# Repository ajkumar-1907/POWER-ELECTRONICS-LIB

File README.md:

<div align="center">

# ⚡ power-converter-lib

**An open-source KiCad library of power electronics converters and embedded hardware.**
Every project ships with a schematic, PCB layout, Gerbers, working principle, design equations and build notes, ready to study, modify or send to fab.

[Projects](#-projects) · [Specs at a glance](#-specs-at-a-glance) · [Folder layout](#-what-each-folder-contains) · [Quick start](#-quick-start) · [Roadmap](#-roadmap)

</div>

---

## 🖼️ Gallery

Click any board to open its folder.

<table>
  <tr>
    <td align="center" width="25%">
      <br/>
      <b><a href="buck-converter/">Buck Converter</a></b><br/><sub>DC-DC · Step-down</sub>
    </td>
    <td align="center" width="25%">
      <br/>
      <b><a href="boost-converter/">Boost Converter</a></b><br/><sub>DC-DC · Step-up</sub>
    </td>
    <td align="center" width="25%">
      <br/>
      <b><a href="ac-dc-bridge-rectifier/">AC-DC Bridge Rectifier</a></b><br/><sub>AC-DC · Full-wave</sub>
    </td>
    <td align="center" width="25%">
      <br/>
      <b><a href="transformerless-power-supply/">Transformerless PSU</a></b><br/><sub>AC-DC · Capacitive dropper</sub>
    </td>
  </tr>
  <tr>
    <td align="center">
      <br/>
      <b><a href="dc-motor-speed-controller/">DC Motor Speed Controller</a></b><br/><sub>Motor control · PWM</sub>
    </td>
    <td align="center">
      <br/>
      <b><a href="servo-tester/">Servo Tester</a></b><br/><sub>Motor control · 555 PWM</sub>
    </td>
    <td align="center">
      <br/>
      <b><a href="usb-to-uart-converter/">USB to UART Converter</a></b><br/><sub>Interface · CP2102N</sub>
    </td>
    <td align="center">
      <br/>
      <b><a href="air-quality-monitor/">IoT Air Quality Monitor</a></b><br/><sub>IoT · ESP8266</sub>
    </td>
  </tr>
  <tr>
    <td align="center">
      <br/>
      <b><a href="airtap/">AirTap</a></b><br/><sub>Home automation · Touchless switch</sub>
    </td>
    <td align="center">
      <br/>
      <b><a href="dual-active-bridge/">Dual Active Bridge</a></b><br/><sub>DC-DC · Bidirectional, isolated · 3.3 kW</sub>
    </td>
  </tr>
</table>

---

## 📦 Projects

### 🔋 DC-DC Converters

| Project | Topology | Key IC | Input → Output | Highlights |
|---|---|---|---|---|
| [**Buck Converter**](buck-converter/) | Step-down (non-isolated) | LM2596S-5 | 7–40 V DC → **5 V**, 3 A | 150 kHz switcher, 33 µH inductor, Schottky freewheel |
| [**Boost Converter**](boost-converter/) | Step-up (non-isolated) | XL6009 | 5–32 V DC → **adj. up to ~35 V** | 4 A switch, 400 kHz, multi-turn trimmer, thermal-via array |
| [**Dual Active Bridge**](dual-active-bridge/) | Bidirectional, isolated (2 × full bridge) | C3M0060065K SiC + UCC21520 | **400 V ↔ 350 V**, 3.3 kW | 20 kHz phase-shift control, V2G-ready, 3 isolated domains, reinforced-isolated V/I sensing. ⚠️ High voltage |

### 🔌 AC-DC Converters

| Project | Topology | Key Parts | Input → Output | Highlights |
|---|---|---|---|---|
| [**AC-DC Bridge Rectifier**](ac-dc-bridge-rectifier/) | Full-wave bridge + C filter | 1N4007 ×4, 1000 µF | 12 V AC → **~15.6 V DC** (unregulated) | Bleeder resistor, LED indicator, THT-only |
| [**Transformerless Power Supply**](transformerless-power-supply/) | Capacitive dropper + LDO | X2 2.2 µF, LM7805 | 230 V AC → **5 V DC** | ⚠️ Non-isolated, mains voltage. Read the design notes |

### ⚙️ Motor Control & Signal

| Project | Topology | Key IC | Supply | Highlights |
|---|---|---|---|---|
| [**DC Motor Speed Controller**](dc-motor-speed-controller/) | 555 PWM + low-side switch | NE555 + TIP122 | 5–15 V DC, up to ~3 A | Constant-frequency PWM, 1–99 % duty, flyback diode |
| [**Servo Tester**](servo-tester/) | 555 astable, diode-steered | NE555 | 6 V DC | ~0.85–2.4 ms pulse, pot control, no code needed |

### 🧩 Interface & IoT

| Project | Function | Key IC | Supply | Highlights |
|---|---|---|---|---|
| [**USB to UART Converter**](usb-to-uart-converter/) | USB-C ↔ serial bridge | CP2102N | USB 5 V | ESD protection, TX/RX LEDs, DTR auto-reset |
| [**IoT Air Quality Monitor**](air-quality-monitor/) | Wi-Fi gas-sensing node | ESP-12E + MQ-135 | USB-C / Li-ion | TP4056 charger, MT3608 boost, CH340C auto-flash, OLED |

### 🏠 Home Automation

| Project | Function | Key IC | Supply | Highlights |
|---|---|---|---|---|
| [**AirTap**](airtap/) | Touchless AC relay switch | ATmega328 + VL53L0X | 220 V AC (HLK-5M05) | Hand-wave switching (10–30 mm), fused + MOV-protected, relay/buzzer/LEDs, test firmware. Fork of [ProxiWave-D](https://github.com/ampnics/Proxiwave-D) (MIT) |

---

## 📊 Specs at a glance

| Project | Category | Board Size | Layers | Assembly | 3D Views | KiCad Source |
|---|---|---|:---:|---|:---:|:---:|
| [Buck Converter](buck-converter/) | DC-DC | 51 × 36 mm | 2 | SMD + THT | — | ✅ |
| [Boost Converter](boost-converter/) | DC-DC | 45 × 20 mm | 2 | SMD + THT | ✅ | ✅ |
| [AC-DC Bridge Rectifier](ac-dc-bridge-rectifier/) | AC-DC | 34.6 × 30.1 mm | 2 | THT | — | ⏳ Gerbers only |
| [Transformerless PSU](transformerless-power-supply/) | AC-DC | 48.8 × 37.5 mm | 2 | THT | — | ✅ |
| [DC Motor Speed Controller](dc-motor-speed-controller/) | Motor control | 56.5 × 29 mm | 2 | THT | ✅ | ✅ |
| [Servo Tester](servo-tester/) | Signal | 30.5 × 27.8 mm | 2 | THT | — | ✅ |
| [USB to UART Converter](usb-to-uart-converter/) | Interface | 31 × 15 mm | 2 | SMD (0201, QFN) | — | ✅ |
| [IoT Air Quality Monitor](air-quality-monitor/) | IoT | 68 × 47.4 mm | 2 | SMD + THT | ✅ | ✅ |
| [AirTap](airtap/) | Home automation | 50 × 100 mm | 2 | SMD + THT | ✅ | ✅ |
| [Dual Active Bridge](dual-active-bridge/) | DC-DC (isolated) | 220 × 150 mm | 4 | SMD + THT | ✅ | ✅ |

---

## 🗂️ What each folder contains

Every project follows the same layout, so once you know one you know them all:

```
<project-name>/
├── README.md                     ← overview, working principle, equations, BOM, design notes
├── <project-name>.kicad_pro      ← KiCad project
├── <project-name>.kicad_sch      ← schematic source
├── <project-name>.kicad_pcb      ← PCB layout source
├── <project-name>-PTH.drl        ← plated drill file
├── <project-name>-NPTH.drl       ← non-plated drill file
├── gerbers/                      ← fab-ready Gerber set
├── schematic.png / .svg          ← schematic preview
├── pcb-layout2.png               ← KiCad editor-style layout
├── pcb-layout.png                ← top & bottom render
└── pcb-3d-*.png                  ← 3D renders (where available)
```

Each project README follows the same outline: **Overview → Working Principle → Key Equations → Applications → Specifications → BOM → Design Notes → Pros & Cons → Files → How to Use**.

---

## 🚀 Quick start

```bash
# 1. Clone the library
git clone https://github.com/ajkumar-1907/power-converter-lib.git
cd power-converter-lib

# 2. Open any project in KiCad 10+
#    e.g. boost-converter/boost-converter.kicad_pro
```

### 🏭 Ordering a PCB

1. Open the project folder you want.
2. Zip the contents of `gerbers/` **together with** the two `.drl` files.
3. Upload the zip to any PCB fab (JLCPCB, PCBWay, etc.). The default 2-layer, 1.6 mm FR-4 settings work for every board here except the Dual Active Bridge, which needs **4 layers, 2 oz copper**.
4. **Read the project's Design Notes before ordering.** Some boards list parts that need values set or ratings checked.

---

## 🤝 Contributing

Contributions are welcome: new topologies, layout improvements, corrections to equations or BOMs.

1. Fork the repo and create a branch (`git checkout -b add-sepic-converter`).
2. Add your project as a new folder that follows the [standard layout](#-what-each-folder-contains).
3. Open a pull request describing the design and how it was verified.

Found a mistake? [Open an issue](https://github.com/ajkumar-1907/power-converter-lib/issues).

---

## ⚠️ Safety

Several projects work with **mains voltage** or **high currents**. The Transformerless Power Supply and AirTap connect directly to mains, the Dual Active Bridge runs at **400 V DC** with large stored capacitor energy, and the Transformerless Power Supply in particular is **not isolated**: every point on it, including the output, can be at lethal potential. Only build these if you understand the risks, and always read each project's Design Notes first.

---

## 📄 License

Released under the [MIT License](LICENSE): free to use, modify and build on, including commercially.

<div align="center">

Designed by **[Anuj Kumar](https://github.com/ajkumar-1907)**, B.Tech Electrical Engineering, Delhi Technological University

⭐ If this library helped you, consider starring the repo!

</div>

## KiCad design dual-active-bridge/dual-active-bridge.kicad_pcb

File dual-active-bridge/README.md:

# Dual Active Bridge (DAB): 3.3 kW Bidirectional DC-DC Converter

A **3.3 kW, 400 V ↔ 350 V bidirectional isolated DC-DC power stage** for EV battery charging with **V2G (vehicle-to-grid)** capability. The board has two SiC full bridges connected through an off-board high-frequency transformer and series inductor. Power flows in either direction, set by the phase shift between the two bridges.

> **B.Tech Major Project-I (2026-27)**, Dept. of Electrical Engineering, Delhi Technological University. Anuj Kumar (23EE039) and Ankush (23EE033).

> ⚠️ **DANGER: 400 V DC.** The DC-link and battery capacitors store lethal energy and stay charged after power is removed. Bring the board up step by step (see [How to Use](#how-to-use)) and always measure before touching.

### 3D views

| Top | Bottom |
|---|---|
|  |  |

### Schematic sections

| Bridge 1 (primary, 400 V) | Bridge 2 (secondary, 350 V) |
|---|---|
|  |  |
| **Isolated gate drive** | **Isolated V / I sensing** |
|  |  |

### Layer views (4-layer)

| L1 Front copper | L4 Back copper |
|---|---|
|  |  |
| **L2 In1: V1+ / V2+ / GND planes** | **L3 In2: PGND1 / PGND2 / +5 V planes** |
|  |  |

## Overview

| Block | Parts | Function |
|---|---|---|
| **Bridge 1 (primary)** | Q1–Q4 C3M0060065K, C1 100 µF/450 V, C3/C4 film + C7/C8 1812 | 400 V DC bus full bridge: legs A and B |
| **Bridge 2 (secondary)** | Q5–Q8 C3M0060065K, C2 150 µF/450 V, C5/C6 film + C9/C10 1812 | 350 V battery-side full bridge: legs C and D |
| **Gate drive** | U1–U4 UCC21520DW, PS1–PS8 MGJ2D051505SC | One dual isolated driver per leg and one isolated +15 / −5 V supply per switch (Kelvin-source return) |
| **Voltage sensing** | R30–R41 dividers, U5/U6 AMC1311B, PS9/PS10 + U7/U8 | Reinforced-isolated V1 and V2 measurement for the controller ADC |
| **Current sensing** | CS1/CS2 LEM LTSR 25-NP | Battery current (I_BAT) and transformer current (I_XFMR) |
| **Protection** | F1/F2 20 A 500 VDC fuses, R46/R47 220 k bleeders | Input/output fusing and capacitor discharge |
| **Control interface** | J9 2×10 header, J10 aux 5 V, D9/D10 OR-ing, U9 3.3 V LDO | 8 PWM inputs, enable, sense outputs to a C2000 LaunchPad |
| **Power terminals** | J1–J8 M4 bolt pads | DC bus ±, battery ±, transformer a/b (primary) and c/d (secondary) |

The board is split into **three isolated domains**:
- **Primary** (PGND1, 400 V)
- **Secondary** (PGND2, 350 V)
- **Control** (GND, 3.3/5 V)

Only the isolators cross between domains. Each one sits over a **2 mm routed slot**, with **≥ 8 mm** creepage/clearance between domains.

## Working Principle

1. **Two square waves.** Each full bridge switches at **20 kHz** with 50 % duty, diagonal pairs together (Q1+Q4 / Q2+Q3 on the primary, Q5+Q8 / Q6+Q7 on the secondary). Bridge 1 puts ±V1 on the transformer primary, and Bridge 2 puts ±V2 on the secondary.
2. **Phase shift sets power.** The controller delays Bridge 2 relative to Bridge 1 by a phase angle φ. The voltage difference across the series inductance Lk drives the current that transfers power.
3. **Bidirectional flow.** If φ > 0 (Bridge 1 leads), power flows from the DC bus to the battery (charging, G2V). If φ < 0, power flows from the battery back to the bus (V2G). The hardware is identical in both directions.
4. **Soft switching.** With the turns ratio matched to the voltages (d = n·V2 / V1 ≈ 1), the inductor current commutates each switch's output capacitance during the dead time. This gives **zero-voltage switching (ZVS)** over most of the load range.
5. **Isolation.** The 8:7 transformer gives galvanic isolation between bus and battery. The control side is isolated from both through the drivers, the AMC1311s and the LEM sensors.

## J9: Control Header (2×10, to the controller)

| Pin | Signal | Pin | Signal |
|---|---|---|---|
| 1 | PWM1 (Q1) | 2 | PWM2 (Q2) |
| 3 | PWM3 (Q3) | 4 | PWM4 (Q4) |
| 5 | PWM5 (Q5) | 6 | PWM6 (Q6) |
| 7 | PWM7 (Q7) | 8 | PWM8 (Q8) |
| 9 | GND | 10 | GND |
| 11 | DIS (low = enable) | 12 | reserved (fault) |
| 13 | V1 sense + | 14 | V1 sense − |
| 15 | V2 sense + | 16 | V2 sense − |
| 17 | I_BAT | 18 | I_XFMR |
| 19 | +5 V | 20 | GND |

PWMn drives Qn directly. The controller firmware creates the diagonal pairing and the phase shift. Each UCC21520 also adds a hardware dead-time floor of about **500 ns** (R_DT = 49.9 k). DIS is pulled up, so all drivers stay **off** until the controller pulls DIS low.

## Key Equations

**Power transfer (single phase shift):**
```
P = n·V1·V2·φ·(π − |φ|) / (2π²·fs·Lk)        φ in rad, n = N1/N2 = 8/7

P_max (φ = π/2) = n·V1·V2 / (8·fs·Lk)
               = (8/7)(400)(350) / (8 · 20 kHz · 291 µH) ≈ 3.44 kW
At 3.3 kW:  φ ≈ 72°  (≈ 10 µs of the 50 µs period)
```

**Voltage conversion ratio (ZVS condition):**
```
d = n·V2 / V1 = (8/7)(350) / 400 = 1.0     → ZVS on both bridges over a wide load range
```

**Dead time (UCC21520):**
```
t_DT ≈ 10 ns/kΩ × R_DT = 10 × 49.9 k ≈ 500 ns     (1 % of the 50 µs period)
```

**Voltage sense divider (per bus):**
```
V_sense = V_bus × 8.06 k / (5 × 402 k + 8.06 k)  → 500 V gives 2.0 V (AMC1311 full scale)
```

## Applications

- On-board / off-board EV chargers with **V2G / V2H** capability
- Battery energy storage interfaces (bidirectional DC bus ↔ battery)
- Isolated DC-DC stage after a PFC front end
- Teaching and research platform for DAB modulation (SPS, EPS, DPS, TPS)

## Specifications

| Parameter | Value |
|---|---|
| DC bus (V1) | 400 V DC |
| Battery (V2) | 350 V nominal (300 V min) |
| Rated power | 3.3 kW, bidirectional |
| Switching frequency | 20 kHz |
| Transformer | 8:7, off-board (ETD59 / E65 core) |
| Series inductance Lk | 291 µH, off-board (or transformer leakage) |
| Switches | 8 × Wolfspeed C3M0060065K SiC, 650 V / 60 mΩ, TO-247-4 Kelvin source |
| Gate drive | +15 V / −5 V, 10 Ω on / 4.7 Ω off, 500 ns dead time |
| Isolation | 3 domains, ≥ 8 mm creepage, 2 mm slots under every isolator |
| Control | 3.3 V logic, C2000 LaunchPad (or any MCU with 8 PWM outputs) |
| Board | 220 × 150 mm, **4-layer**, 1.6 mm FR-4, **2 oz copper on all layers**, 6 mounting/heatsink holes |

## Bill of Materials (key parts)

| Ref | Value | Package |
|---|---|---|
| Q1–Q8 | Wolfspeed C3M0060065K (650 V, 60 mΩ SiC) | TO-247-4 |
| U1–U4 | TI UCC21520DW dual isolated gate driver | SOIC-16W |
| PS1–PS10 | Murata MGJ2D051505SC (5 V → +15 / −5 V, 5.2 kV) | SIP (THT) |
| U5, U6 | TI AMC1311BDWV reinforced isolated amplifier | SOIC-8 wide |
| CS1, CS2 | LEM LTSR 25-NP closed-loop current sensor | THT |
| C1 | 100 µF 450 V (Nichicon LGN2W101MELZ25) | Snap-in Ø25 |
| C2 | 150 µF 450 V (Nichicon LGN2W151MELZ30) | Snap-in Ø25 |
| C3–C6 | 1 µF 630 V polypropylene film (WIMA MKS4) | P22.5 mm |
| C7–C10 | 100 nF 1 kV X7R (KEMET C1812C104KDRAC) | 1812 |
| D1–D8 | BAT54J turn-off diode | SOD-323F |
| F1, F2 | 20 A 500 VDC fuse (Littelfuse 505) + clips | 6.3 × 32 mm |
| R46, R47 | 220 k 2 W bleeder | Axial |
| U7, U8 / U9 | 78L05 / AP2112K-3.3 | SOT-89 / SOT-23-5 |
| J9 / J10 | 2×10 2.54 mm header / Phoenix MKDS 2-way 5.08 mm | THT |
| J1–J8 | M4 ring-lug bolt pads | Ø4.3 mm plated |

The full BOM is 174 parts. 0805/1206 passives and their values are shown in the schematic.

## Design Notes

- **Off-board magnetics:** the transformer (8:7) and Lk (291 µH) connect through the M4 bolt pads: a/b to the primary, c/d to the secondary. Size the wires for the RMS current at 3.3 kW.
- **Kelvin source:** every MOSFET has its own isolated supply, referenced to its own Kelvin pin, so 8 supplies in total. Sharing a supply between low-side switches would tie the Kelvin pins together and defeat the Kelvin connection.
- **Commutation loop:** each leg has a film capacitor (top) and a 1 kV 1812 (bottom) placed directly at the MOSFET drain/source pins. V+ and PGND are laminated on In1/In2 to keep loop inductance low.
- **Isolation rules:** the custom DRC file (`dual-active-bridge.kicad_dru`) enforces:
  - 3 mm between different potentials inside a power domain;
  - 8 mm between domains;
  - 2 mm from HV copper to edges and slots.
  
  Netclasses are named `<domain>_<kind>_<potential>`.
- **Gate supply voltage:** the MGJ2D051505SC gives +15 / −5 V. For the recommended −4 V turn-off of the C3M series, use a −4 V variant or add a zener.
- **J9 pin 12** is reserved. The UCC21520 has no fault output, so the pin is free for a future over-current comparator.
- **Aux 5 V (J10):** the 10 isolated supplies draw about 0.5 A, which is more than a LaunchPad's 5 V pin can supply. J10 and J9 +5 V are OR-ed through D9/D10.
- **Heatsinks:** Q1–Q4 and Q5–Q8 mount on two separate heatsinks (H5/H6 mounting holes), one per isolated domain. Use insulating pads.
- **Before ordering:** check the footprints against their datasheets, especially:
  - the TO-247-4 pin order (1 D, 2 S, 3 Kelvin S, 4 G);
  - the AMC1311 DWV pin-out;
  - the fuse clips.

## Pros & Cons

| Pros | Cons |
|---|---|
| Bidirectional with identical hardware (G2V and V2G) | 8 active switches, 8 isolated gate supplies |
| Galvanic isolation and ZVS at d ≈ 1, giving high efficiency | ZVS is lost at light load or when d ≠ 1 (needs EPS/DPS/TPS modulation) |
| Simple single-phase-shift control | High circulating (reactive) current at light load |
| SiC + Kelvin source: fast, clean switching | Off-board magnetics must be designed and wound separately |
| Reinforced-isolated sensing, ready for closed-loop control | 4-layer, 2 oz board: higher fab cost |

## Files in This Folder

| File | Description |
|---|---|
| `dual-active-bridge.kicad_pro` / `.kicad_sch` / `.kicad_pcb` | KiCad 10 project, root schematic and PCB |
| `Bridge1` / `Bridge2` / `GateDrive` / `Sensing` / `Connectors.kicad_sch` | Hierarchical sub-sheets |
| `dual-active-bridge.kicad_dru` | Custom HV / isolation design rules |
| `DAB_3k3W.kicad_sym` / `DAB_3k3W.pretty/` | Project symbol library and fuse-clip footprint (loaded through `sym-lib-table` / `fp-lib-table`) |
| `dual-active-bridge-PTH.drl` / `dual-active-bridge-NPTH.drl` | Drill files |
| `gerbers/` | Gerber set for fabrication: 4 copper layers, masks, paste, silkscreen, Edge.Cuts with isolation slots, job file |
| `schematic.pdf` | Full 6-sheet schematic |
| `schematic.png` / `schematic-*.png` | Root sheet and section images |
| `pcb-3d-top.png` / `pcb-3d-bottom.png` / `pcb-3d-angle.png` / `pcb-3d-angle-rear.png` | 3D renders |
| `pcb-layout2.png` / `pcb-layout.png` | Layout previews |
| `pcb-front-copper.png` / `pcb-back-copper.png` / `pcb-inner1-copper.png` / `pcb-inner2-copper.png` | Copper layer views |

## How to Use

1. Open `dual-active-bridge.kicad_pro` in [KiCad](https://www.kicad.org/) 10 or later.
2. **To manufacture:**
   - Zip `gerbers/` together with the two `.drl` files and upload the zip.
   - Order **4 layers, 1.6 mm, 2 oz copper on all layers**.
   - In the order notes, mention that the board has **internal routed slots**. They are drawn on Edge.Cuts.
3. **Assemble:** the 1812 capacitors C7–C10 are on the bottom side. Mount Q1–Q8 on insulated heatsinks.
4. **Bring up in stages:**
   1. 5 V only: check every gate waveform with DIS low and no HV applied.
   2. 24–48 V on V1, current-limited, with a resistive load on V2.
   3. Step up to 400 V under supervision, behind a shield, with the fuses fitted.
5. **Close the loop:** read V1, V2, I_BAT and I_XFMR on the controller's ADC and regulate power with the phase shift φ.

## License

Released under the repository's [MIT License](../LICENSE).

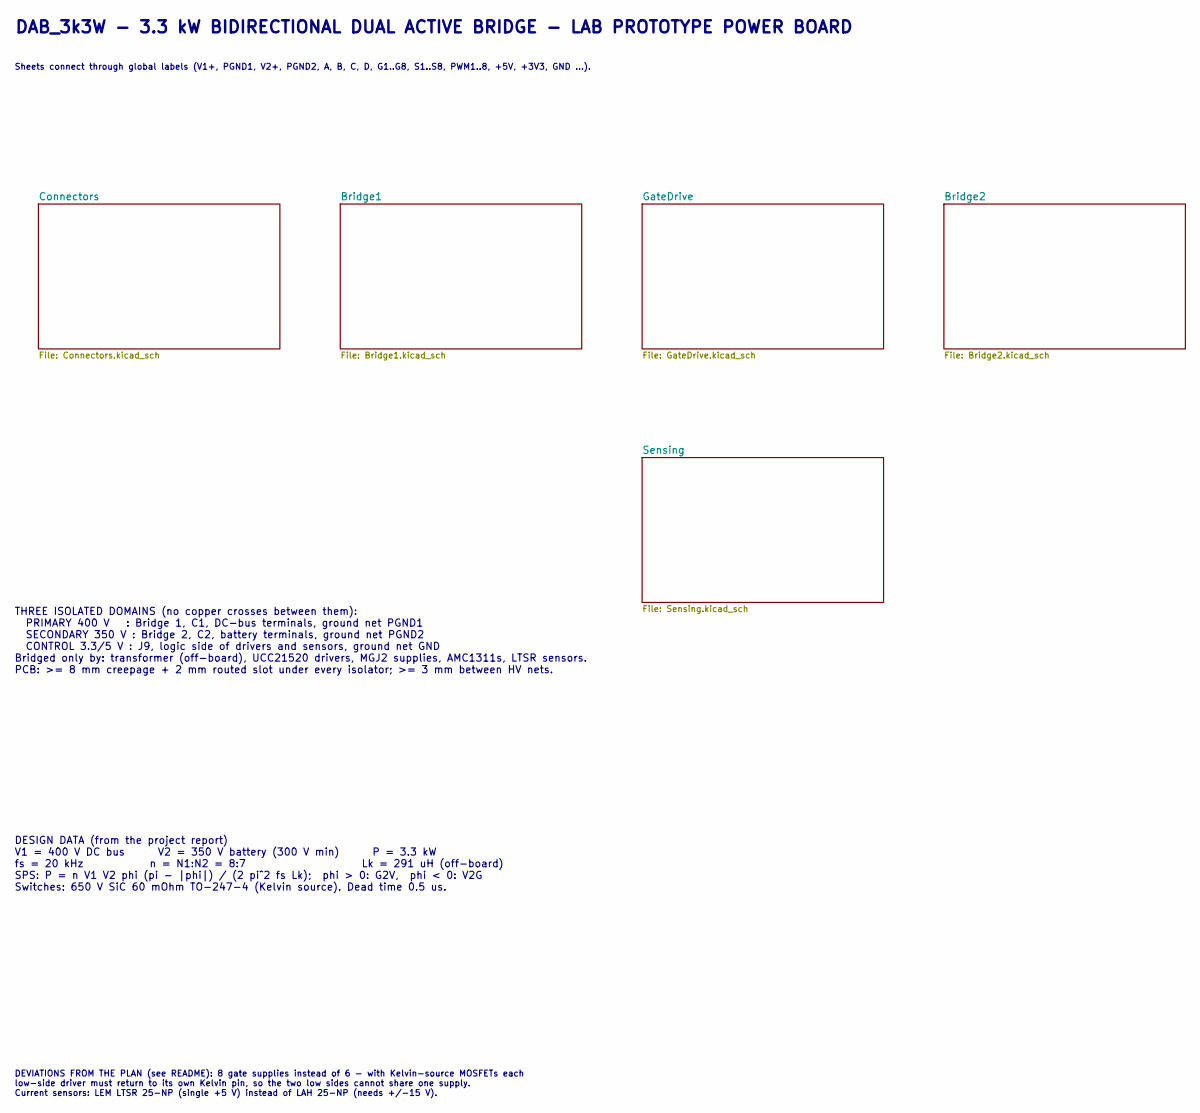
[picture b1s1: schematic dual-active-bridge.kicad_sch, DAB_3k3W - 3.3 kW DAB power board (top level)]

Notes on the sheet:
DEVIATIONS FROM THE PLAN (see README): 8 gate supplies instead of 6 - with Kelvin-source MOSFETs each low-side driver must return to its own Kelvin pin, so the two low sides cannot share one supply. Current sensors: LEM LTSR 25-NP (single +5 V) instead of LAH 25-NP (needs +/-15 V).
DAB_3k3W - 3.3 kW BIDIRECTIONAL DUAL ACTIVE BRIDGE - LAB PROTOTYPE POWER BOARD
Sheets connect through global labels (V1+, PGND1, V2+, PGND2, A, B, C, D, G1..G8, S1..S8, PWM1..8, +5V, +3V3, GND ...).
DESIGN DATA (from the project report) V1 = 400 V DC bus V2 = 350 V battery (300 V min) P = 3.3 kW fs = 20 kHz n = N1:N2 = 8:7 Lk = 291 uH (off-board) SPS: P = n V1 V2 phi (pi - |phi|) / (2 pi^2 fs Lk); phi > 0: G2V, phi < 0: V2G Switches: 650 V SiC 60 mOhm TO-247-4 (Kelvin source). Dead time 0.5 us.
THREE ISOLATED DOMAINS (no copper crosses between them): PRIMARY 400 V : Bridge 1, C1, DC-bus terminals, ground net PGND1 SECONDARY 350 V : Bridge 2, C2, battery terminals, ground net PGND2 CONTROL 3.3/5 V : J9, logic side of drivers and sensors, ground net GND Bridged only by: transformer (off-boa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

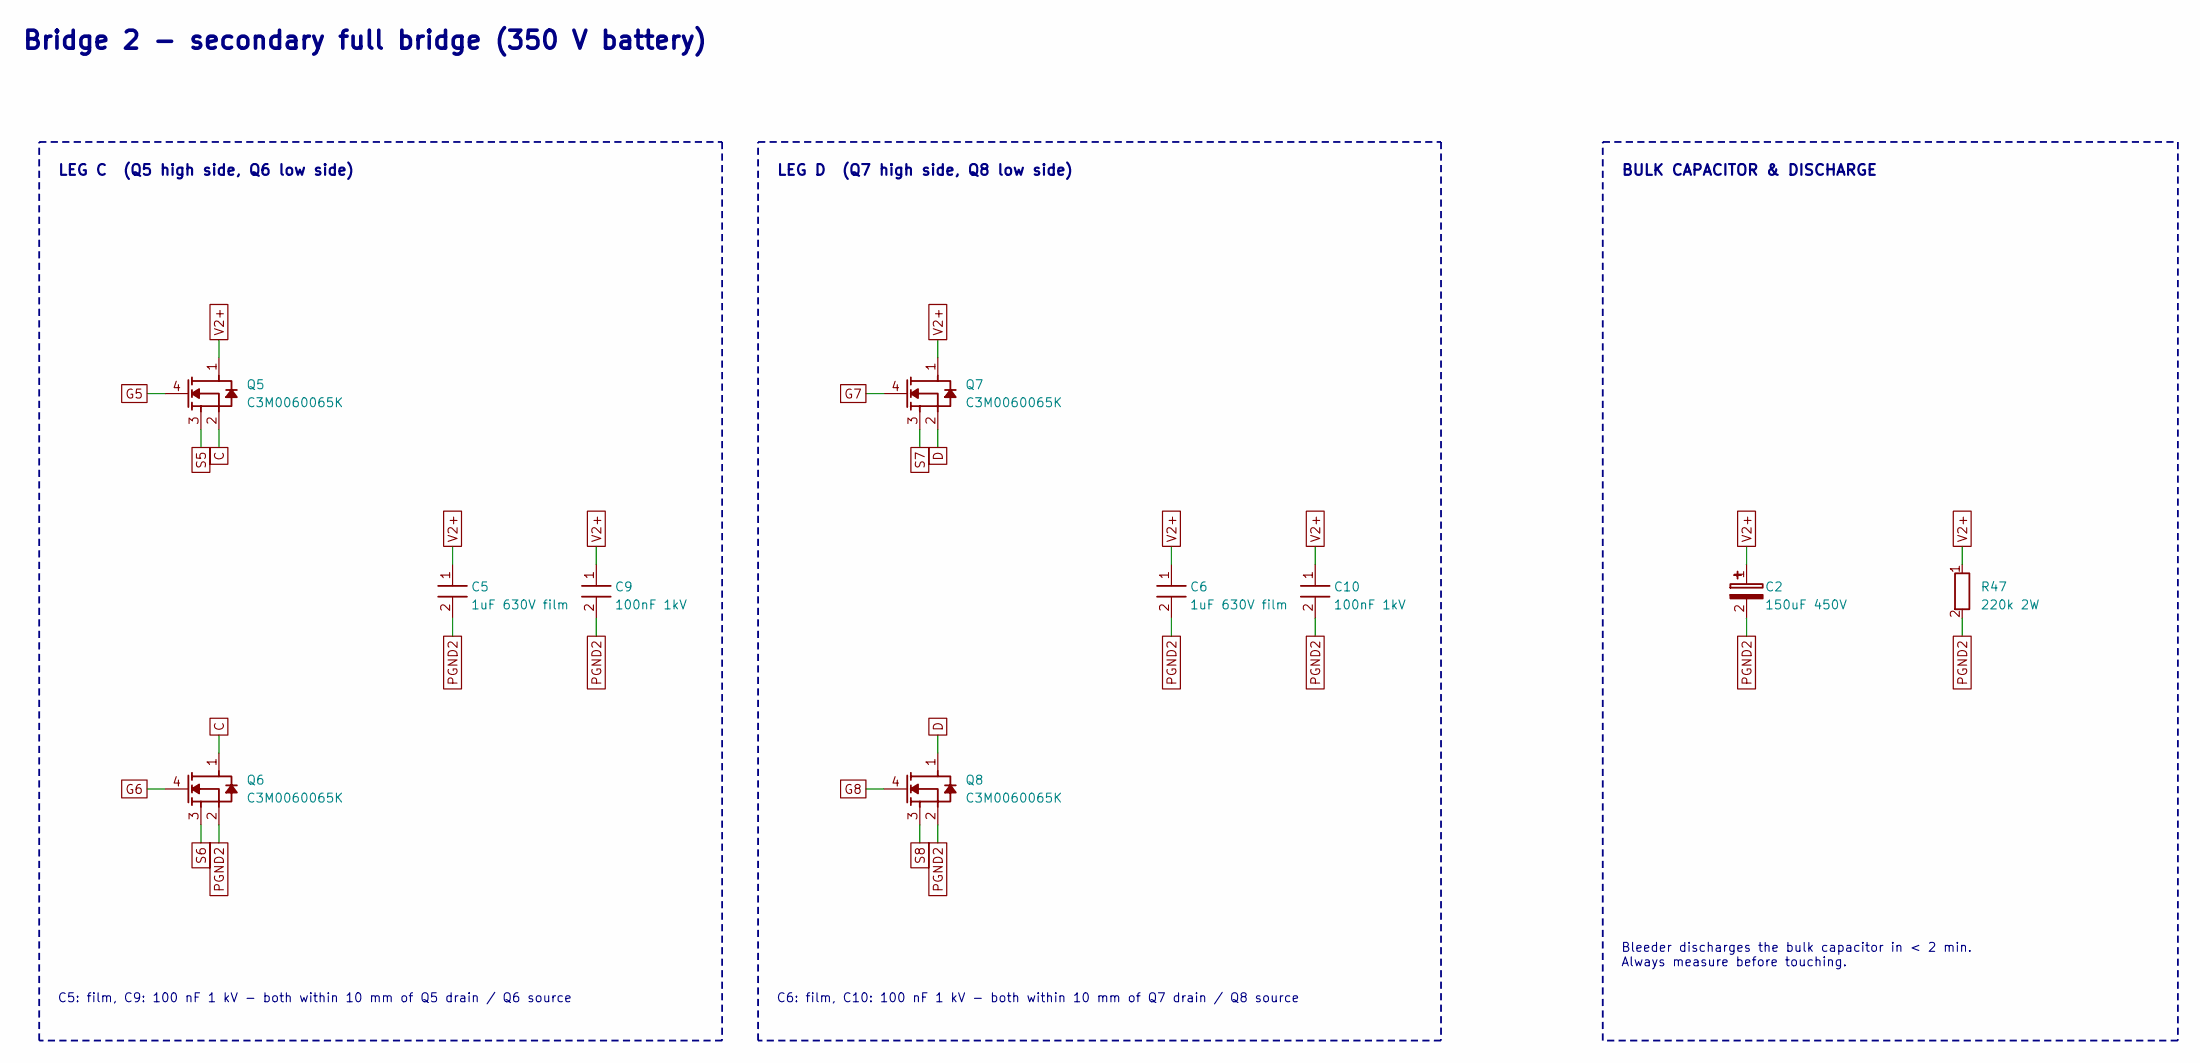
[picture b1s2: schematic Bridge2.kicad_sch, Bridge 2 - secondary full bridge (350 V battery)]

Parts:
C2: 150uF 450V; CP_Radial_D25.0mm_P10.00mm_SnapIn; MPN Nichicon LGN2W151MELZ30
C5, C6: 1uF 630V film; C_Rect_L26.5mm_W11.5mm_P22.50mm_MKS4; MPN WIMA MKS4 1uF 630VDC, P22.5 (or KEMET R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
C9, C10: 100nF 1kV; C_1812_4532Metric; MPN KEMET C1812C104KDRAC (1 kV X7R)
Q5, Q6, Q7, Q8: C3M0060065K; TO-247-4_Vertical; MPN Wolfspeed C3M0060065K
R47: 220k 2W; R_Axial_DIN0617_L17.0mm_D6.0mm_P25.40mm_Horizontal; MPN Vishay PR02000202203JR500

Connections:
C: Q5.2 (S), Q6.1 (D); also elsewhere on the board
D: Q7.2 (S), Q8.1 (D); also elsewhere on the board
G5: Q5.4 (G); also elsewhere on the board
G6: Q6.4 (G); also elsewhere on the board
G7: Q7.4 (G); also elsewhere on the board
G8: Q8.4 (G); also elsewhere on the board
PGND2: C2.2, C5.2, C6.2, C9.2, C10.2, Q6.2 (S), Q8.2 (S), R47.2; also elsewhere on the board
S5: Q5.3 (KS); also elsewhere on the board
S6: Q6.3 (KS); also elsewhere on the board
S7: Q7.3 (KS); also elsewhere on the board
S8: Q8.3 (KS); also elsewhere on the board
V2+: C2.1, C5.1, C6.1, C9.1, C10.1, Q5.1 (D), Q7.1 (D), R47.1; also elsewhere on the board

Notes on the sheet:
Bridge 2 - secondary full bridge (350 V battery)
LEG C (Q5 high side, Q6 low side)
C6: film, C10: 100 nF 1 kV - both within 10 mm of Q7 drain / Q8 source
LEG D (Q7 high side, Q8 low side)
Bleeder discharges the bulk capacitor in < 2 min. Always measure before touching.
C5: film, C9: 100 nF 1 kV - both within 10 mm of Q5 drain / Q6 source
BULK CAPACITOR & DISCHARGE

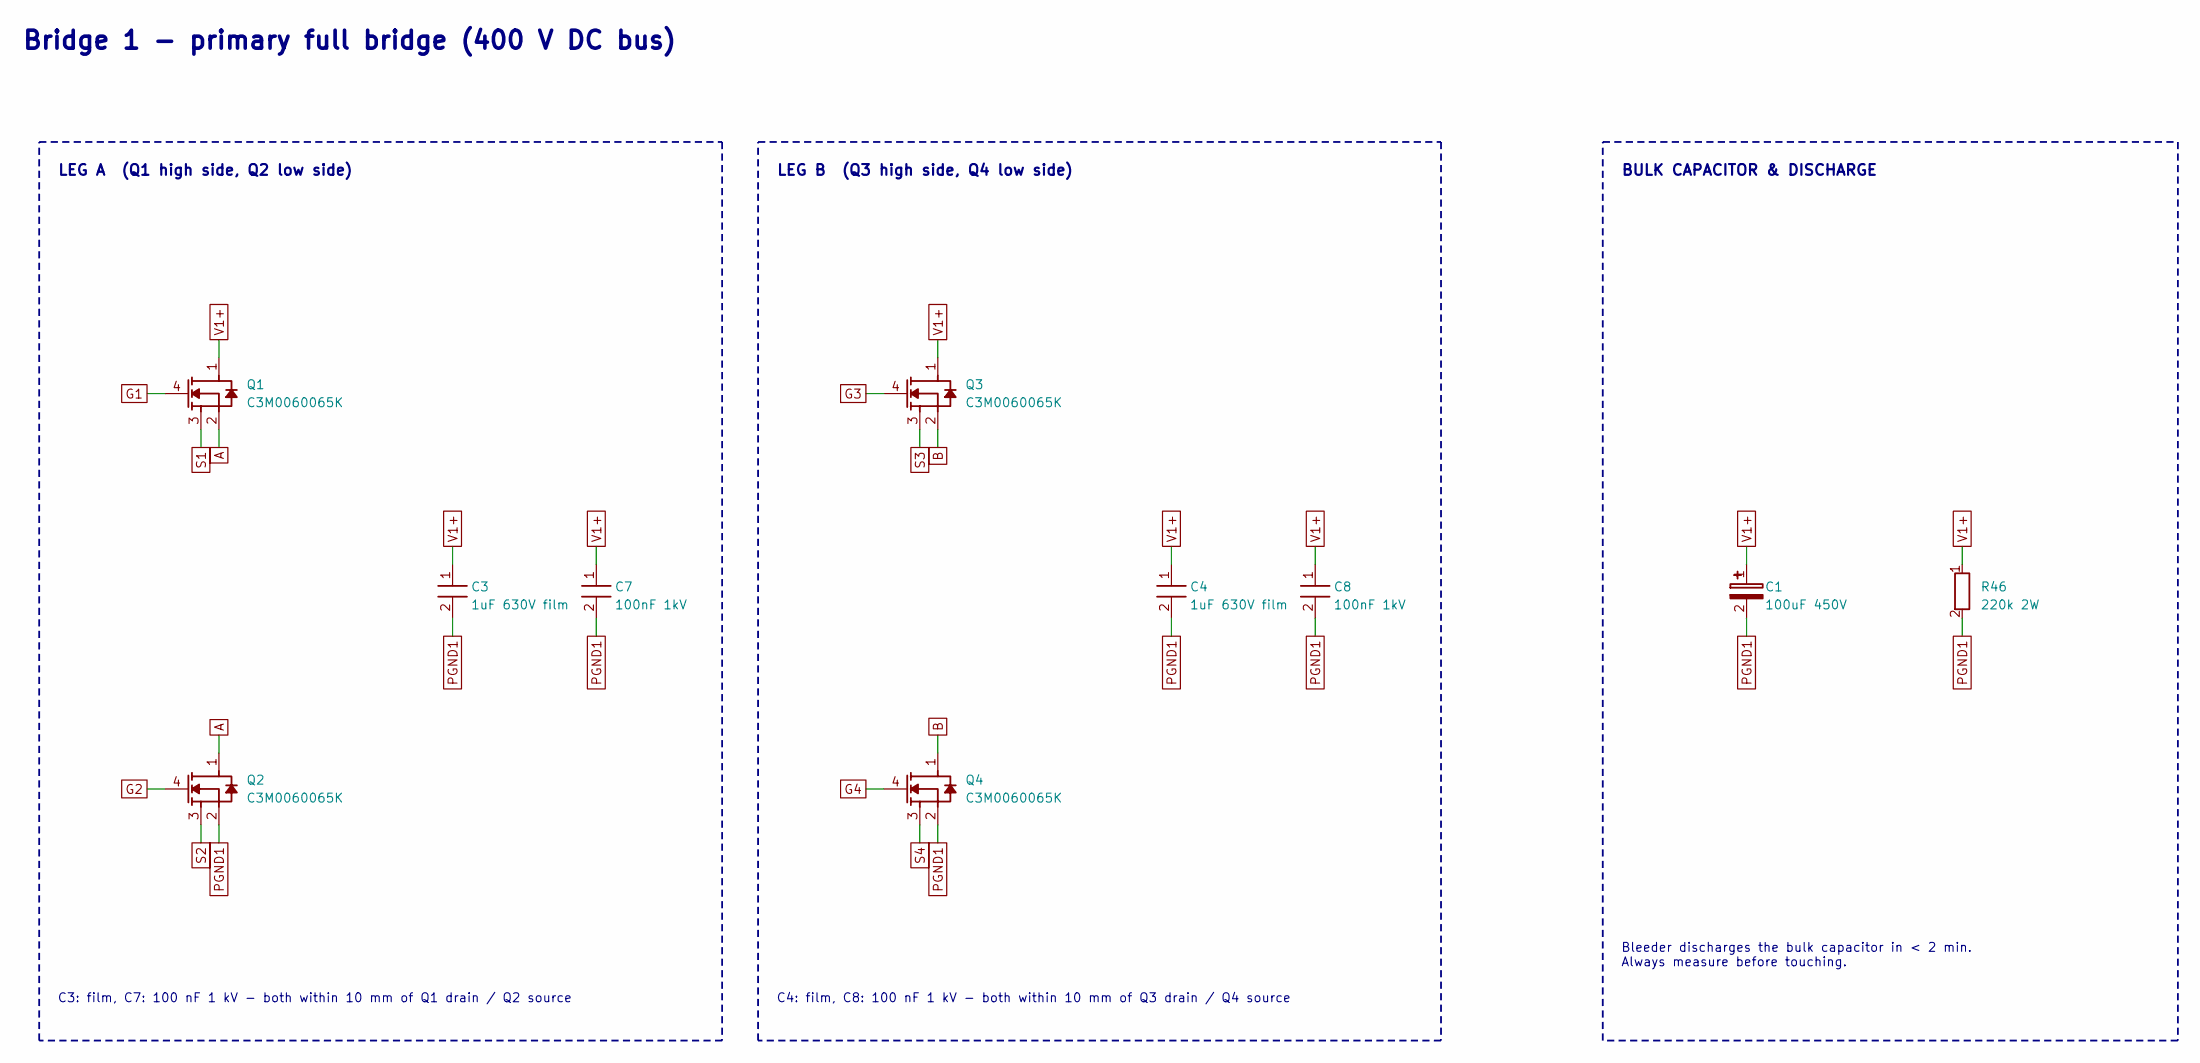
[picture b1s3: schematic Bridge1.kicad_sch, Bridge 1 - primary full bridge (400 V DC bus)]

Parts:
C1: 100uF 450V; CP_Radial_D25.0mm_P10.00mm_SnapIn; MPN Nichicon LGN2W101MELZ25
C3, C4: 1uF 630V film; C_Rect_L26.5mm_W11.5mm_P22.50mm_MKS4; MPN WIMA MKS4 1uF 630VDC, P22.5 (or KEMET R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
C7, C8: 100nF 1kV; C_1812_4532Metric; MPN KEMET C1812C104KDRAC (1 kV X7R)
Q1, Q2, Q3, Q4: C3M0060065K; TO-247-4_Vertical; MPN Wolfspeed C3M0060065K
R46: 220k 2W; R_Axial_DIN0617_L17.0mm_D6.0mm_P25.40mm_Horizontal; MPN Vishay PR02000202203JR500

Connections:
A: Q1.2 (S), Q2.1 (D); also elsewhere on the board
B: Q3.2 (S), Q4.1 (D); also elsewhere on the board
G1: Q1.4 (G); also elsewhere on the board
G2: Q2.4 (G); also elsewhere on the board
G3: Q3.4 (G); also elsewhere on the board
G4: Q4.4 (G); also elsewhere on the board
PGND1: C1.2, C3.2, C4.2, C7.2, C8.2, Q2.2 (S), Q4.2 (S), R46.2; also elsewhere on the board
S1: Q1.3 (KS); also elsewhere on the board
S2: Q2.3 (KS); also elsewhere on the board
S3: Q3.3 (KS); also elsewhere on the board
S4: Q4.3 (KS); also elsewhere on the board
V1+: C1.1, C3.1, C4.1, C7.1, C8.1, Q1.1 (D), Q3.1 (D), R46.1; also elsewhere on the board

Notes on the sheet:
C3: film, C7: 100 nF 1 kV - both within 10 mm of Q1 drain / Q2 source
Bleeder discharges the bulk capacitor in < 2 min. Always measure before touching.
LEG A (Q1 high side, Q2 low side)
Bridge 1 - primary full bridge (400 V DC bus)
C4: film, C8: 100 nF 1 kV - both within 10 mm of Q3 drain / Q4 source
LEG B (Q3 high side, Q4 low side)
BULK CAPACITOR & DISCHARGE

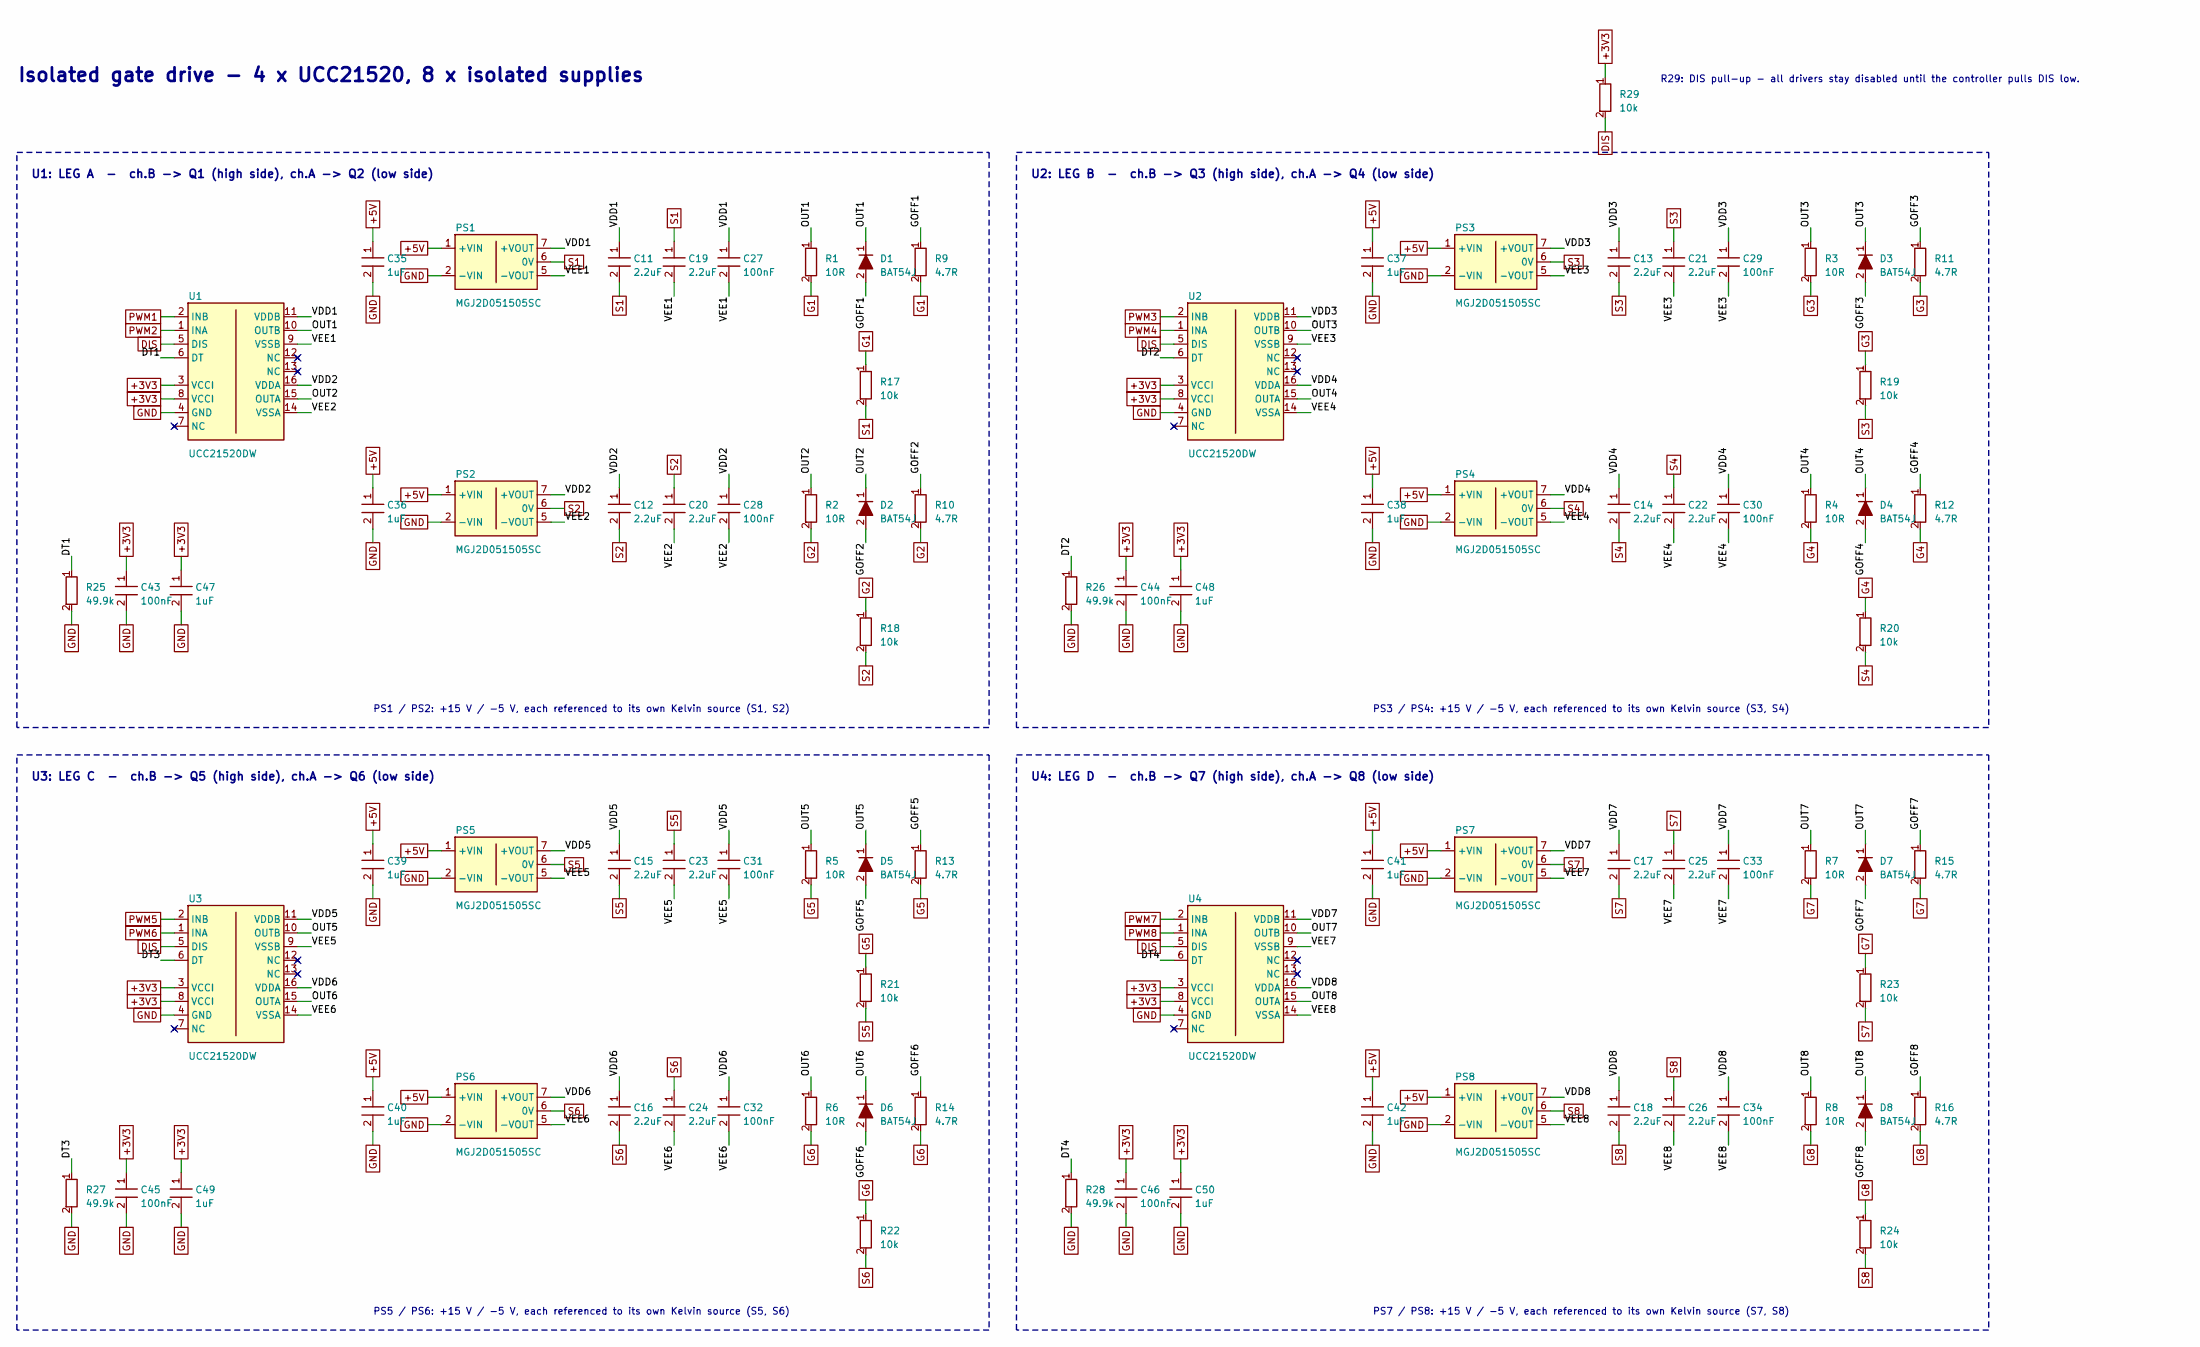
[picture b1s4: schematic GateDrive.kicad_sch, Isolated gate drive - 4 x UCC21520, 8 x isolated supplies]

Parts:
C11, C12, C13, C14, C15, C16, C17, C18, C19, C20, C21, C22, C23, C24, C25, C26: 2.2uF; C_0805_2012Metric
C27, C28, C29, C30, C31, C32, C33, C34: 100nF; C_1206_3216Metric
C35, C36, C37, C38, C39, C40, C41, C42, C47, C48, C49, C50: 1uF; C_0805_2012Metric
C43, C44, C45, C46: 100nF; C_0805_2012Metric
D1, D2, D3, D4, D5, D6, D7, D8: BAT54J; D_SOD-323F; MPN Nexperia BAT54J
PS1, PS2, PS3, PS4, PS5, PS6, PS7, PS8: MGJ2D051505SC; Converter_DCDC_Murata_MGJ2DxxxxxxSC_THT; MPN Murata MGJ2D051505SC
R1, R2, R3, R4, R5, R6, R7, R8: 10R; R_0805_2012Metric
R9, R10, R11, R12, R13, R14, R15, R16: 4.7R; R_0805_2012Metric
R17, R18, R19, R20, R21, R22, R23, R24, R29: 10k; R_0805_2012Metric
R25, R26, R27, R28: 49.9k; R_0805_2012Metric
U1, U2, U3, U4: UCC21520DW; SOIC-16W_7.5x10.3mm_P1.27mm; MPN TI UCC21520DW

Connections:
+3V3: C43.1, C44.1, C45.1, C46.1, C47.1, C48.1, C49.1, C50.1, R29.1, U1.3 (VCCI), U1.8 (VCCI), U2.3 (VCCI), U2.8 (VCCI), U3.3 (VCCI), U3.8 (VCCI), U4.3 (VCCI), U4.8 (VCCI); also elsewhere on the board
+5V: C35.1, C36.1, C37.1, C38.1, C39.1, C40.1, C41.1, C42.1, PS1.1 (+VIN), PS2.1 (+VIN), PS3.1 (+VIN), PS4.1 (+VIN), PS5.1 (+VIN), PS6.1 (+VIN), PS7.1 (+VIN), PS8.1 (+VIN); also elsewhere on the board
/GateDrive/DT1: R25.1, U1.6 (DT)
/GateDrive/DT2: R26.1, U2.6 (DT)
/GateDrive/DT3: R27.1, U3.6 (DT)
/GateDrive/DT4: R28.1, U4.6 (DT)
/GateDrive/GOFF1: D1.2 (A), R9.1
/GateDrive/GOFF2: D2.2 (A), R10.1
/GateDrive/GOFF3: D3.2 (A), R11.1
/GateDrive/GOFF4: D4.2 (A), R12.1
/GateDrive/GOFF5: D5.2 (A), R13.1
/GateDrive/GOFF6: D6.2 (A), R14.1
/GateDrive/GOFF7: D7.2 (A), R15.1
/GateDrive/GOFF8: D8.2 (A), R16.1
/GateDrive/OUT1: D1.1 (K), R1.1, U1.10 (OUTB)
/GateDrive/OUT2: D2.1 (K), R2.1, U1.15 (OUTA)
/GateDrive/OUT3: D3.1 (K), R3.1, U2.10 (OUTB)
/GateDrive/OUT4: D4.1 (K), R4.1, U2.15 (OUTA)
/GateDrive/OUT5: D5.1 (K), R5.1, U3.10 (OUTB)
/GateDrive/OUT6: D6.1 (K), R6.1, U3.15 (OUTA)
/GateDrive/OUT7: D7.1 (K), R7.1, U4.10 (OUTB)
/GateDrive/OUT8: D8.1 (K), R8.1, U4.15 (OUTA)
/GateDrive/VDD1: C11.1, C27.1, PS1.7 (+VOUT), U1.11 (VDDB)
/GateDrive/VDD2: C12.1, C28.1, PS2.7 (+VOUT), U1.16 (VDDA)
/GateDrive/VDD3: C13.1, C29.1, PS3.7 (+VOUT), U2.11 (VDDB)
/GateDrive/VDD4: C14.1, C30.1, PS4.7 (+VOUT), U2.16 (VDDA)
/GateDrive/VDD5: C15.1, C31.1, PS5.7 (+VOUT), U3.11 (VDDB)
/GateDrive/VDD6: C16.1, C32.1, PS6.7 (+VOUT), U3.16 (VDDA)
/GateDrive/VDD7: C17.1, C33.1, PS7.7 (+VOUT), U4.11 (VDDB)
/GateDrive/VDD8: C18.1, C34.1, PS8.7 (+VOUT), U4.16 (VDDA)
/GateDrive/VEE1: C19.2, C27.2, PS1.5 (-VOUT), U1.9 (VSSB)
/GateDrive/VEE2: C20.2, C28.2, PS2.5 (-VOUT), U1.14 (VSSA)
/GateDrive/VEE3: C21.2, C29.2, PS3.5 (-VOUT), U2.9 (VSSB)
/GateDrive/VEE4: C22.2, C30.2, PS4.5 (-VOUT), U2.14 (VSSA)
/GateDrive/VEE5: C23.2, C31.2, PS5.5 (-VOUT), U3.9 (VSSB)
/GateDrive/VEE6: C24.2, C32.2, PS6.5 (-VOUT), U3.14 (VSSA)
/GateDrive/VEE7: C25.2, C33.2, PS7.5 (-VOUT), U4.9 (VSSB)
/GateDrive/VEE8: C26.2, C34.2, PS8.5 (-VOUT), U4.14 (VSSA)
DIS: R29.2, U1.5 (DIS), U2.5 (DIS), U3.5 (DIS), U4.5 (DIS); also elsewhere on the board
G1: R1.2, R9.2, R17.1; also elsewhere on the board
G2: R2.2, R10.2, R18.1; also elsewhere on the board
G3: R3.2, R11.2, R19.1; also elsewhere on the board
G4: R4.2, R12.2, R20.1; also elsewhere on the board
G5: R5.2, R13.2, R21.1; also elsewhere on the board
G6: R6.2, R14.2, R22.1; also elsewhere on the board
G7: R7.2, R15.2, R23.1; also elsewhere on the board
G8: R8.2, R16.2, R24.1; also elsewhere on the board
GND: C35.2, C36.2, C37.2, C38.2, C39.2, C40.2, C41.2, C42.2, C43.2, C44.2, C45.2, C46.2, C47.2, C48.2, C49.2, C50.2, PS1.2 (-VIN), PS2.2 (-VIN), PS3.2 (-VIN), PS4.2 (-VIN), PS5.2 (-VIN), PS6.2 (-VIN), PS7.2 (-VIN), PS8.2 (-VIN), R25.2, R26.2, R27.2, R28.2, U1.4 (GND), U2.4 (GND), U3.4 (GND), U4.4 (GND); also elsewhere on the board
PWM1: U1.2 (INB); also elsewhere on the board
PWM2: U1.1 (INA); also elsewhere on the board
PWM3: U2.2 (INB); also elsewhere on the board
PWM4: U2.1 (INA); also elsewhere on the board
PWM5: U3.2 (INB); also elsewhere on the board
PWM6: U3.1 (INA); also elsewhere on the board
PWM7: U4.2 (INB); also elsewhere on the board
PWM8: U4.1 (INA); also elsewhere on the board
S1: C11.2, C19.1, PS1.6 (0V), R17.2; also elsewhere on the board
S2: C12.2, C20.1, PS2.6 (0V), R18.2; also elsewhere on the board
S3: C13.2, C21.1, PS3.6 (0V), R19.2; also elsewhere on the board
S4: C14.2, C22.1, PS4.6 (0V), R20.2; also elsewhere on the board
S5: C15.2, C23.1, PS5.6 (0V), R21.2; also elsewhere on the board
S6: C16.2, C24.1, PS6.6 (0V), R22.2; also elsewhere on the board
S7: C17.2, C25.1, PS7.6 (0V), R23.2; also elsewhere on the board
S8: C18.2, C26.1, PS8.6 (0V), R24.2; also elsewhere on the board

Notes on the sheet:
PS7 / PS8: +15 V / -5 V, each referenced to its own Kelvin source (S7, S8)
U1: LEG A - ch.B -> Q1 (high side), ch.A -> Q2 (low side)
R29: DIS pull-up - all drivers stay disabled until the controller pulls DIS low.
U3: LEG C - ch.B -> Q5 (high side), ch.A -> Q6 (low side)
U2: LEG B - ch.B -> Q3 (high side), ch.A -> Q4 (low side)
PS5 / PS6: +15 V / -5 V, each referenced to its own Kelvin source (S5, S6)
U4: LEG D - ch.B -> Q7 (high side), ch.A -> Q8 (low side)
Isolated gate drive - 4 x UCC21520, 8 x isolated supplies
PS3 / PS4: +15 V / -5 V, each referenced to its own Kelvin source (S3, S4)
PS1 / PS2: +15 V / -5 V, each referenced to its own Kelvin source (S1, S2)

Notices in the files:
README.md:
License: MIT
